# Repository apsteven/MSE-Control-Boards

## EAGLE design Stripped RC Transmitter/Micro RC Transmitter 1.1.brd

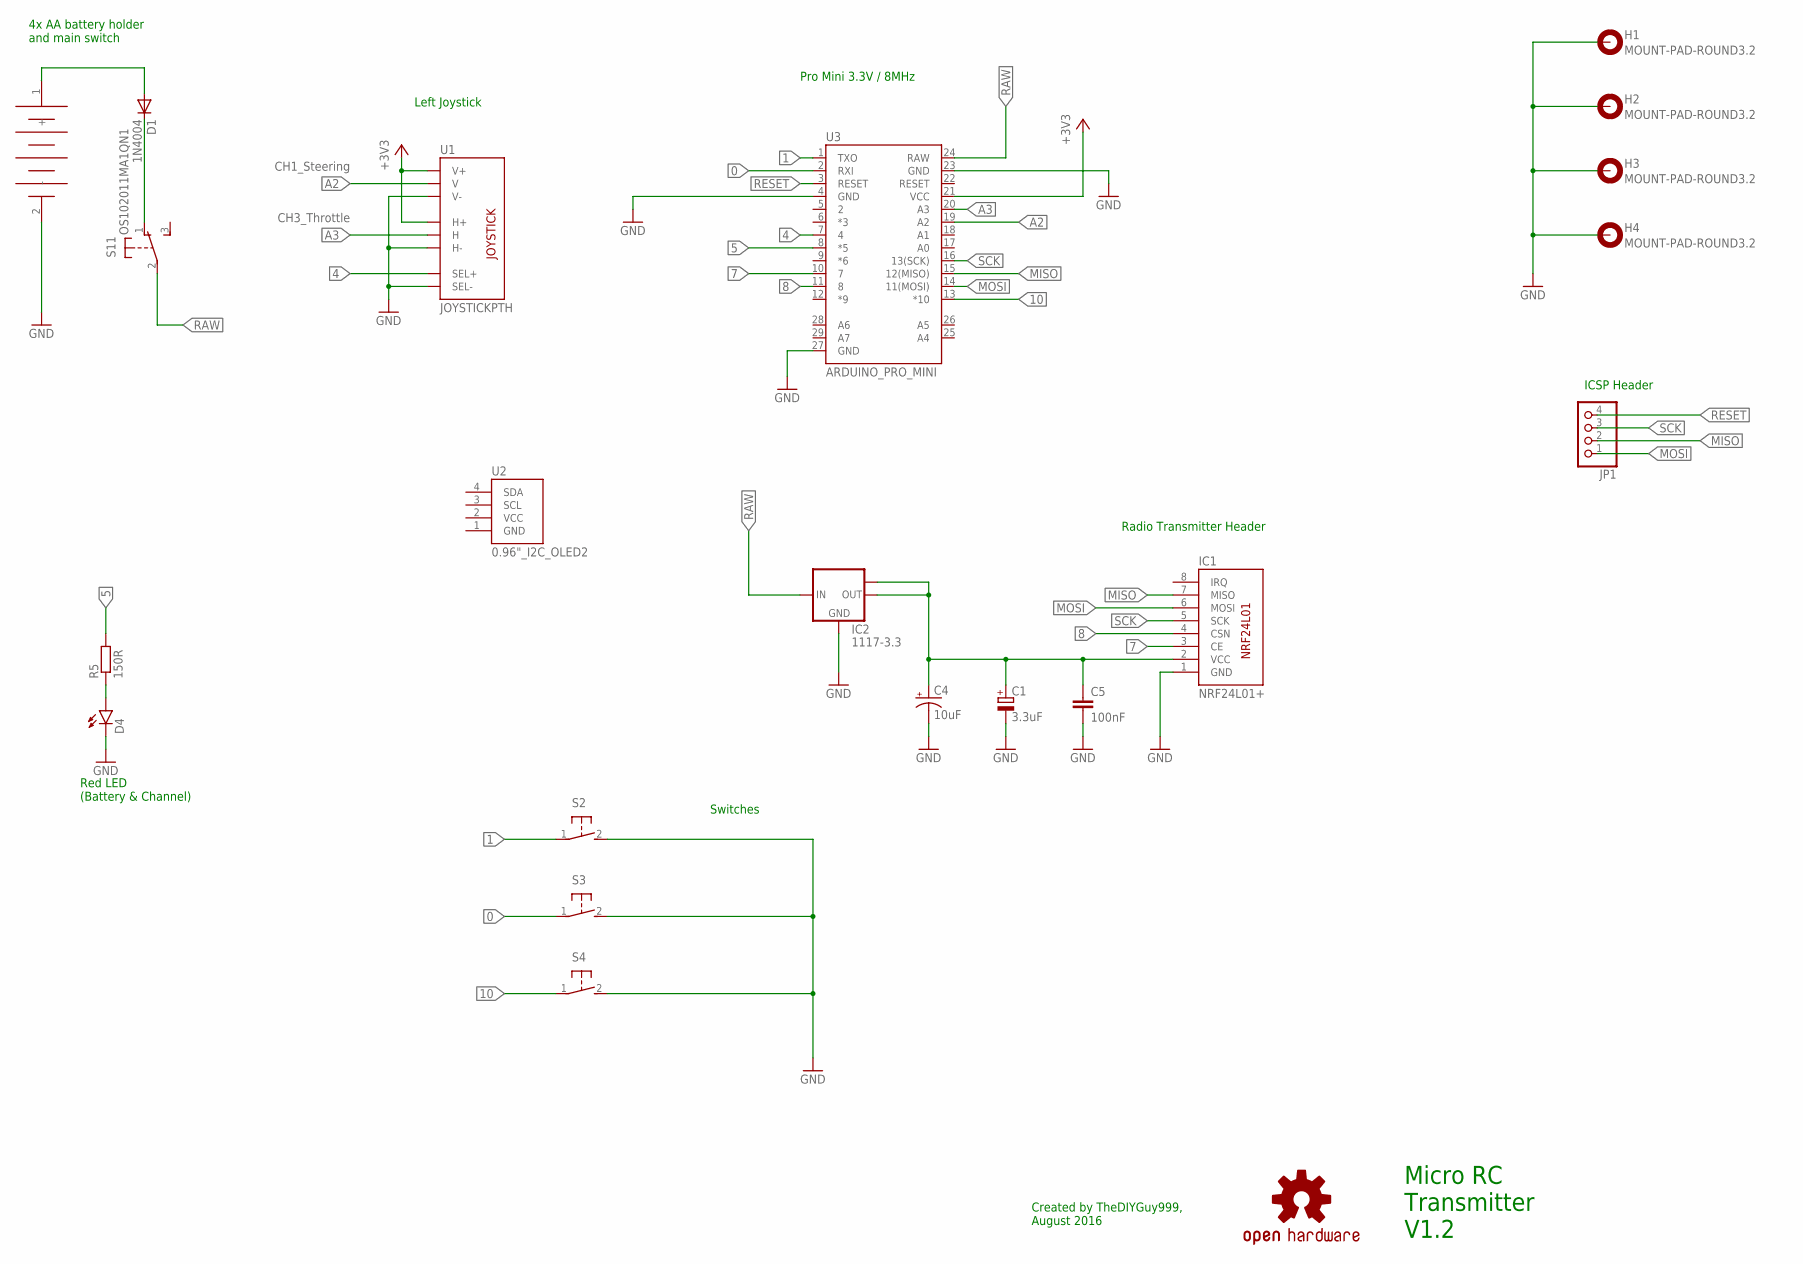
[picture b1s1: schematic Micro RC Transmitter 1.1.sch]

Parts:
C1: 3.3uF; B45181A
C4: 10uF; EIA3216
C5: 100nF; C0805
D1: 1N4004; DO-214AC
D4: LED3MM
G1: 4X_AA_BATTERY_HOLDER
H1, H2, H3, H4: MOUNT-PAD-ROUND3.2; 3,2-PAD
IC1: NRF24L01+; NRF24L01
IC2: 1117-3.3; SOT223
JP1: PINHD-1X4; 1X04
LOGO1: OSHW-LOGOM; OSHW-LOGO-M
R5: 150R; R0805
S1: OS102011MA1QN1
S2, S3, S4: 31-XX; B3F-31XX
U1: JOYSTICKPTH; JOYSTICK
U2: 0.96"_I2C_OLED2; 0.96"_I2C_OLED_2
U3: ARDUINO_PRO_MINI

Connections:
0: S3.1, U3.2 (RXI)
1: S2.1, U3.1 (TXO)
4: U1.B1A (SEL+), U3.7 (4)
5: R5.2, U3.8 (*5)
7: IC1.3 (CE), U3.10 (7)
8: IC1.4 (CSN), U3.11 (8)
10: S4.1, U3.13 (*10)
+3V3: U1.H1 (H+), U1.V1 (V+), U3.21 (VCC)
A2: U1.V2 (V), U3.19 (A2)
A3: U1.H2 (H), U3.20 (A3)
GND: C1.-, C4.C (-), C5.2, D4.K (C), G1.2 (-), H1.B3,2, H2.B3,2, H3.B3,2, H4.B3,2, IC1.1 (GND), IC2.1 (GND), S2.2 (S), S3.2 (S), S4.2 (S), U1.B2A (SEL-), U1.H3 (H-), U1.V3 (V-), U3.4 (GND), U3.23 (GND), U3.27 (GND)
MISO: IC1.7 (MISO), JP1.2, U3.15 (12(MISO))
MOSI: IC1.6 (MOSI), JP1.1, U3.14 (11(MOSI))
unnamed: D4.A, R5.1
unnamed: D1.A, G1.1 (+)
unnamed: D1.C, S1.1 (O)
unnamed: C1.+, C4.A (+), C5.1, IC1.2 (VCC), IC2.2 (OUT), IC2.TAB (OUT1)
RAW: IC2.3 (IN), S1.2, U3.24 (RAW)
RESET: JP1.4, U3.3 (RESET)
SCK: IC1.5 (SCK), JP1.3, U3.16 (13(SCK))

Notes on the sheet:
Micro RC Transmitter V1.2
Radio Transmitter Header
4x AA battery holder and main switch
Left Joystick
Switches
ICSP Header
Pro Mini 3.3V / 8MHz
Created by TheDIYGuy999, August 2016
Red LED (Battery & Channel)
CH1_Steering
CH3_Throttle

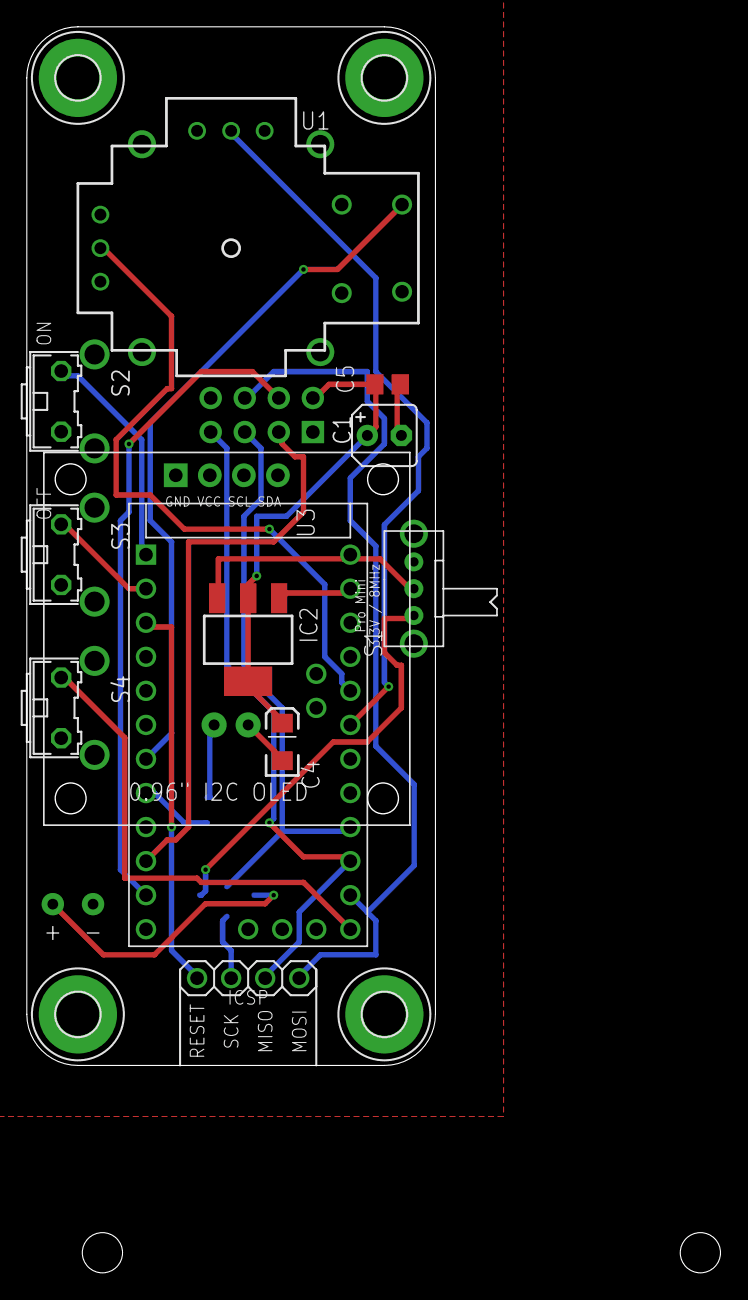
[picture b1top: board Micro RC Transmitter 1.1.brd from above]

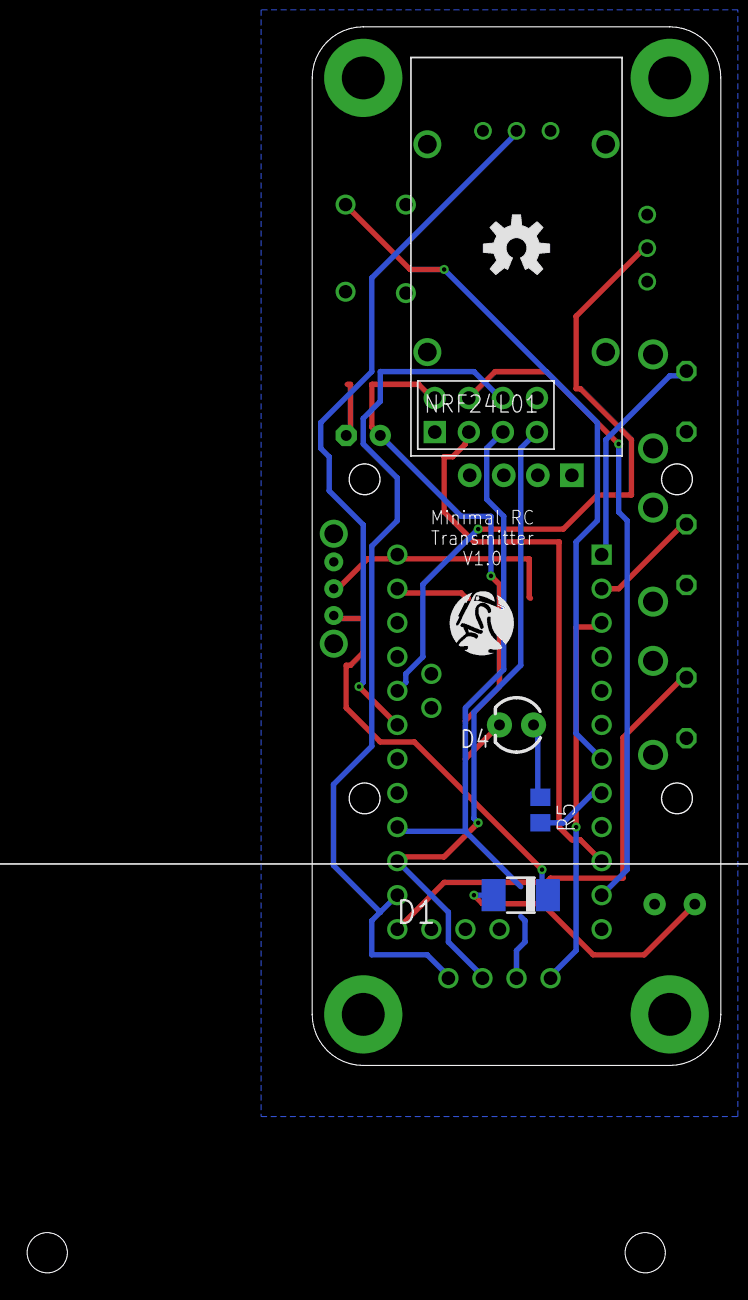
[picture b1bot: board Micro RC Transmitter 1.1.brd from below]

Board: 2 copper layers, 51.7 x 92.9 mm, 23 parts (7 on the bottom side), 20 nets.

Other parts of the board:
LOGO2: OSHW-LOGOM; R2BUILDERS-LOGO

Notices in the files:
parts and their libraries:
SparkFun-Aesthetics: Licensing: Creative Commons ShareAlike 4.0 International - https://creativecommons.org/licenses/by-sa/4.0
